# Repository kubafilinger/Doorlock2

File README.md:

# Doorlock2
Doorlock2 is a new codding in AVR C++, but not developed at this time. Latest developed repository is based on Arduino and is called DoorlockArduino

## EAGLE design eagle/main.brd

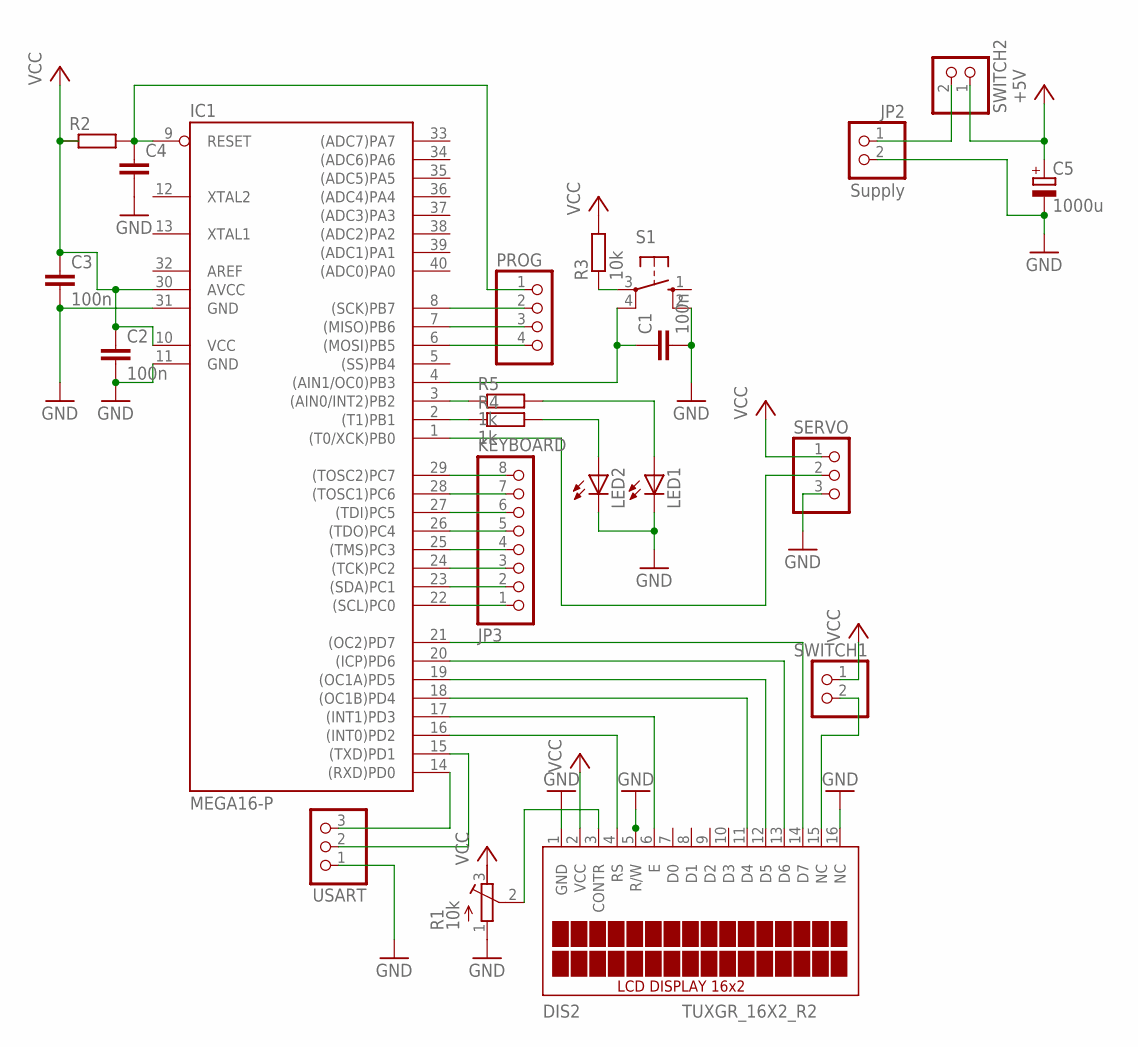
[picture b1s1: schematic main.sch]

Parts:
C1, C2, C3: 100n; C025-025X050
C4: C-EU025-025X050; C025-025X050
C5: 1000u; E2,5-7
DIS2: TUXGR_16X2_R2
IC1: MEGA16-P; DIL40
JP2: Supply; 1X02
JP3: KEYBOARD; 1X08
LED1, LED2: LED5MM
PROG: PINHD-1X4; 1X04
R1: 10k; RTRIM4G/J
R2: R-EU_0204/7; 0204/7
R3: 10k; 0204/7
R4, R5: 1k; 0204/7
S1: 10-XX; B3F-10XX
SERVO: PINHD-1X3; 1X03
SWITCH1, SWITCH2: PINHD-1X2; 1X02
USART: PINHD-1X3; 1X03

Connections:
GND: C1.2, C2.2, C3.2, C4.2, C5.-, DIS2.1 (GND), DIS2.5 (R/W), DIS2.16 (NC), IC1.11 (GND), IC1.31 (GND), JP2.2, LED1.K (C), LED2.K (C), R1.1 (A), S1.2 (S1), SERVO.3, USART.1
unnamed: C4.1, IC1.9 (RESET), PROG.1, R2.2
unnamed: DIS2.14 (D7), IC1.21 ((OC2)PD7)
unnamed: DIS2.13 (D6), IC1.20 ((ICP)PD6)
unnamed: DIS2.12 (D5), IC1.19 ((OC1A)PD5)
unnamed: DIS2.11 (D4), IC1.18 ((OC1B)PD4)
unnamed: DIS2.4 (RS), IC1.16 ((INT0)PD2)
unnamed: DIS2.6 (E), IC1.17 ((INT1)PD3)
unnamed: DIS2.3 (CONTR), R1.2 (S)
unnamed: IC1.2 ((T1)PB1), R4.1
unnamed: IC1.3 ((AIN0/INT2)PB2), R5.1
unnamed: LED2.A, R4.2
unnamed: LED1.A, R5.2
unnamed: IC1.6 ((MOSI)PB5), PROG.4
unnamed: C1.1, IC1.4 ((AIN1/OC0)PB3), S1.4 (P1)
unnamed: JP2.1, SWITCH2.2
unnamed: R3.1, S1.3
unnamed: DIS2.15 (NC), SWITCH1.2
unnamed: IC1.7 ((MISO)PB6), PROG.3
unnamed: IC1.8 ((SCK)PB7), PROG.2
unnamed: IC1.14 ((RXD)PD0), USART.3
unnamed: IC1.15 ((TXD)PD1), USART.2
unnamed: IC1.29 ((TOSC2)PC7), JP3.8
unnamed: IC1.28 ((TOSC1)PC6), JP3.7
unnamed: IC1.27 ((TDI)PC5), JP3.6
unnamed: IC1.26 ((TDO)PC4), JP3.5
unnamed: IC1.25 ((TMS)PC3), JP3.4
unnamed: IC1.24 ((TCK)PC2), JP3.3
unnamed: IC1.23 ((SDA)PC1), JP3.2
unnamed: IC1.22 ((SCL)PC0), JP3.1
unnamed: IC1.1 ((T0/XCK)PB0), SERVO.2
VCC: C2.1, C3.1, C5.+, DIS2.2 (VCC), IC1.10 (VCC), IC1.30 (AVCC), R1.3 (E), R2.1, R3.2, SWITCH1.1, SWITCH2.1

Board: 2 copper layers, 22 parts (0 on the bottom side), 32 nets, no tracks yet.

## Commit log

2018-03-26 Main cpp file + gitignore + uml diagram
2018-04-11 Add LCD library
2018-04-11 Object implemet and def.
2018-04-15 Move git repo lever up, becouse fo good works i need AS proj
2018-04-16 Init LCD and basic menu for tests. New method for user object
2018-04-17 Keyboard object and simple use
2018-04-18 Implement keyboard
2018-04-18 Change user code from int to string. Basic sign in
2018-04-19 Fix code compare for login action
2018-04-23 Add user role
2018-04-23 Basic functionalities. Main menu
2018-04-23 working on menu navigation
2018-04-23 Menu class
2018-04-24 Test eeprome
2018-06-04 Add helpers lib and add serialize method to user object
2018-06-06 Add logout to menu list
2018-06-06 Add logout to menu list and reset menu method
2018-06-06 Working on save users to eeprom
2018-06-06 Refactor
2018-06-13 Add usart lib but not working
2018-06-18 Refactor usart header file
2018-06-18 Refactor doc
2018-06-18 Remove two methods and improve setters for name, code. Test create object from eeprom
2018-06-18 Eeprom not working. Read problem
2018-06-18 Add info display functionality (errors and other informations aletr)
2018-06-18 Change pin
2018-06-19 Servo delay implement
2018-07-08 Add eagle schema project to repo
